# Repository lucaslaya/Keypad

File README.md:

# Keypad
Directional arrow keys, 4 Macro keys, 1 Knob, Display

## Part Selection
https://jlcpcb.com/parts
### MCU
- RP2040: Seeed Studio XIAO RP2040
### Input Devices
- EC-11 Rotary Encoder (with push button)
### Display
- I2C OLED Display: SSD1306
### Connectivity
- USB-C Breakout Board
- ESD Protection Diode: TPD2E001
### Key switches
- Cherry MX Red
- 1N4148 Diodes

## Keyboard Specs
### Keycaps/Switches 
Dimensions in mm represent a 1u key
- Keycap and Switch Sizes (https://hirosarts.com/blog/keycap-dimensions-guide-for-beginners/?srsltid=AfmBOoqFAn7m0XP5UFBrCiC00yMLdIinkfjyP8Adn-44h1oWgLyK09f7)
  - 
- Key Layout
  -

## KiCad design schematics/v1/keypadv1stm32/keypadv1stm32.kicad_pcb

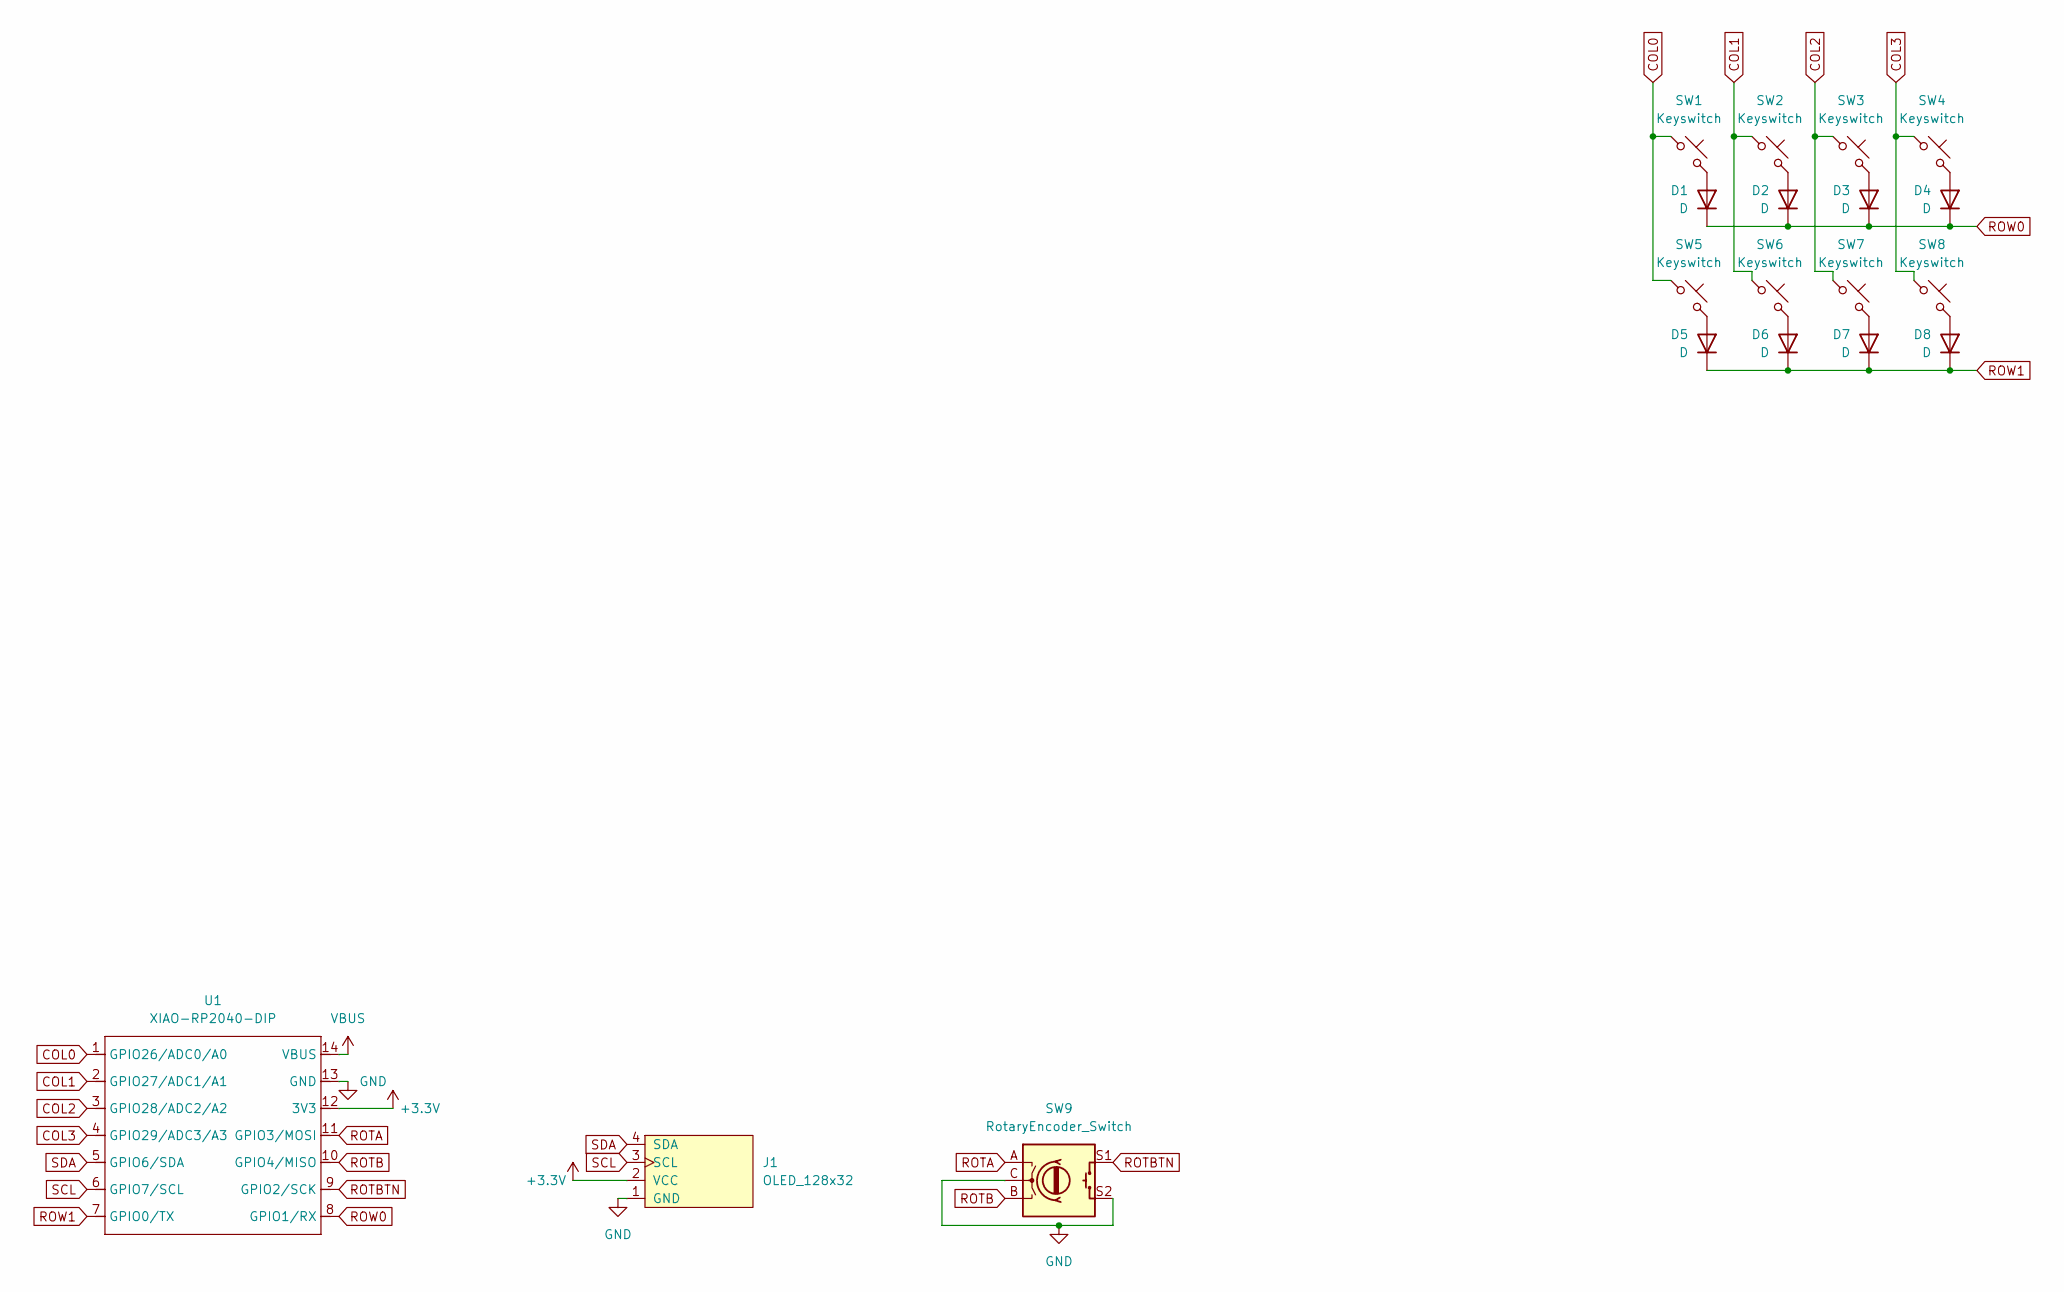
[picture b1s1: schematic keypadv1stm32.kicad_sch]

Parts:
D1, D2, D3, D4, D5, D6, D7, D8: D; D_SOD-123
J1: OLED_128x32; Adafruit_SSD1306
SW1, SW2, SW3, SW4, SW5, SW6, SW7, SW8: Keyswitch; SW_Cherry_MX_1.00u_PCB
SW9: RotaryEncoder_Switch; RotaryEncoder_Alps_EC11E-Switch_Vertical_H20mm
U1: XIAO-RP2040-DIP; XIAO-RP2040-SMD

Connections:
+3.3V: J1.2 (VCC), U1.12 (3V3)
COL0: SW1.1, SW5.1, U1.1 (GPIO26/ADC0/A0)
COL1: SW2.1, SW6.1, U1.2 (GPIO27/ADC1/A1)
COL2: SW3.1, SW7.1, U1.3 (GPIO28/ADC2/A2)
COL3: SW4.1, SW8.1, U1.4 (GPIO29/ADC3/A3)
GND: J1.1 (GND), SW9.C, SW9.S2, U1.13 (GND)
unnamed: D1.2 (A), SW1.2
unnamed: D2.2 (A), SW2.2
unnamed: D3.2 (A), SW3.2
unnamed: D4.2 (A), SW4.2
unnamed: D5.2 (A), SW5.2
unnamed: D6.2 (A), SW6.2
unnamed: D7.2 (A), SW7.2
unnamed: D8.2 (A), SW8.2
ROTA: SW9.A, U1.11 (GPIO3/MOSI)
ROTB: SW9.B, U1.10 (GPIO4/MISO)
ROTBTN: SW9.S1, U1.9 (GPIO2/SCK)
ROW0: D1.1 (K), D2.1 (K), D3.1 (K), D4.1 (K), U1.8 (GPIO1/RX)
ROW1: D5.1 (K), D6.1 (K), D7.1 (K), D8.1 (K), U1.7 (GPIO0/TX)
SCL: J1.3 (SCL), U1.6 (GPIO7/SCL)
SDA: J1.4 (SDA), U1.5 (GPIO6/SDA)
VBUS: U1.14 (VBUS)

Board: 2 copper layers, 19 parts (0 on the bottom side), 21 nets, no tracks yet.

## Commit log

2025-07-11 Added v0 schematic
2025-07-13 Added schematics
2025-07-14 Rev2 first edition
2025-07-14 Rev2
2025-07-14 Updated fimware folder
